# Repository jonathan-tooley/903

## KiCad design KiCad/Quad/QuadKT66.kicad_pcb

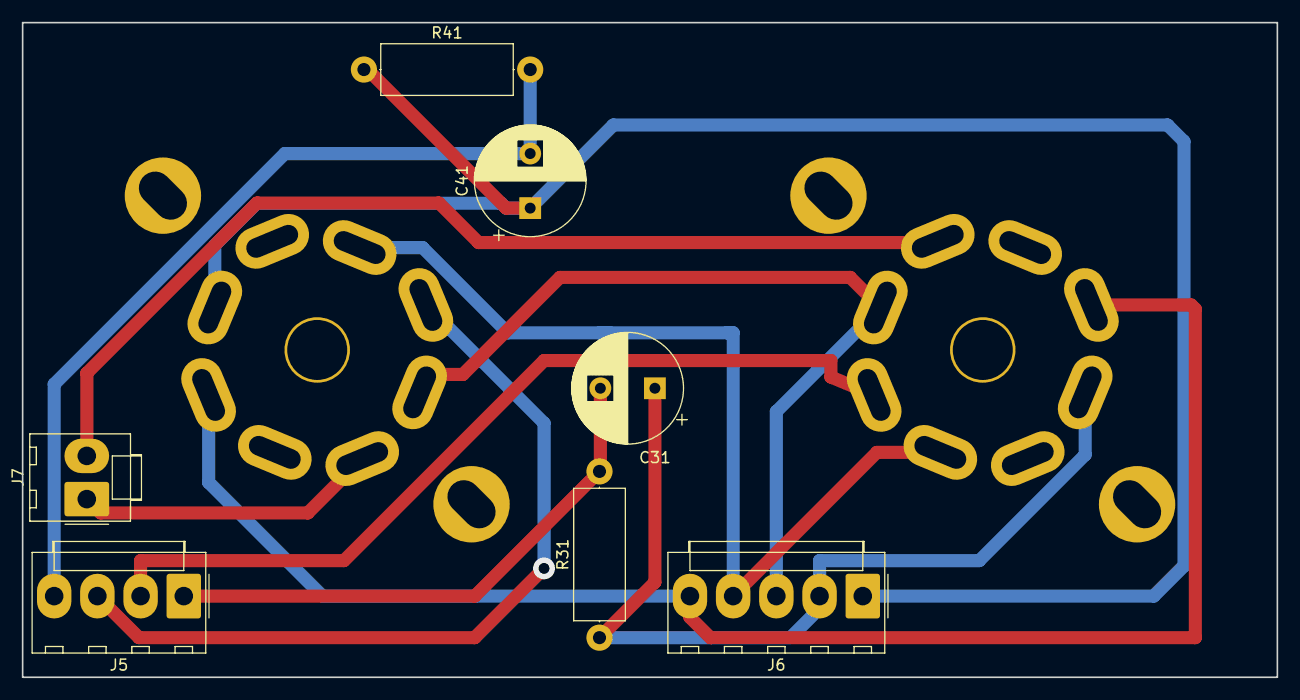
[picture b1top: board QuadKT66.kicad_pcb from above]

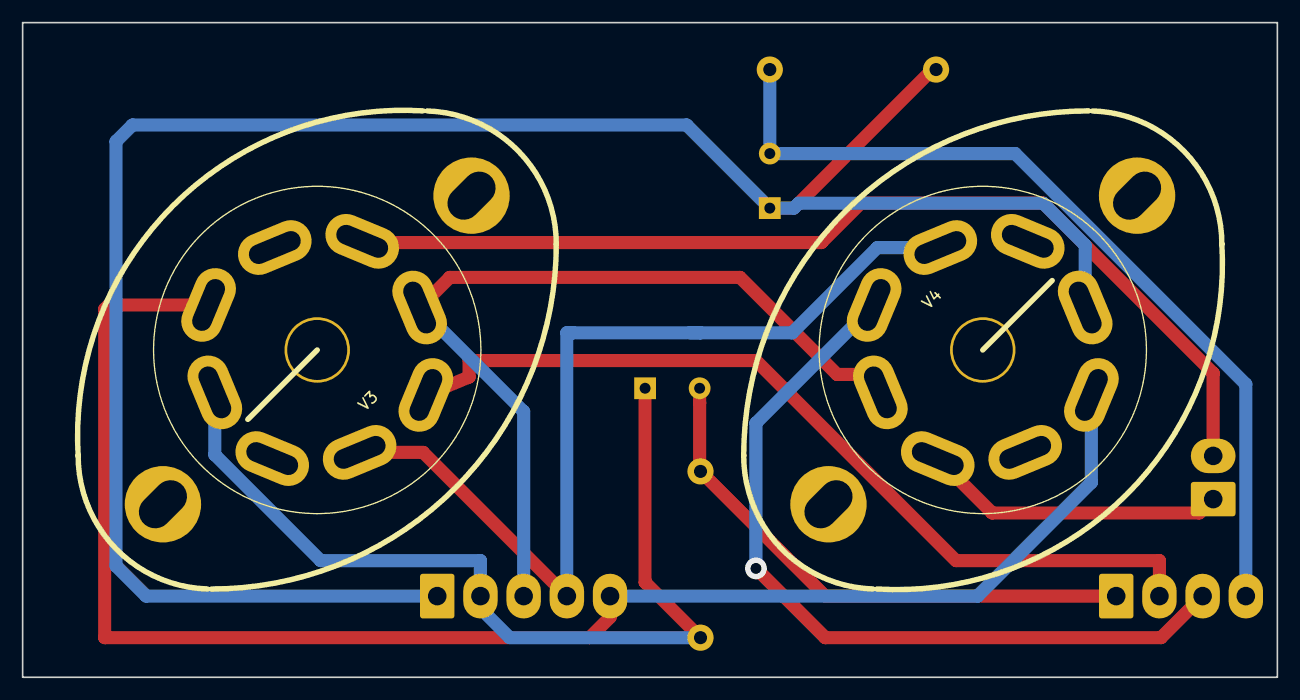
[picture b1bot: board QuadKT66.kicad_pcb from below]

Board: 2 copper layers, 115.0 x 60.0 mm, 9 parts (2 on the bottom side), 11 nets.

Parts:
C31, C41: 470u; CP_Radial_D10.0mm_P5.00mm
J5: Molex_KK-396_A-41791-0004_1x04_P3.96mm_Vertical
J6: Molex_KK-396_A-41791-0005_1x05_P3.96mm_Vertical
J7: Molex_KK-396_A-41791-0002_1x02_P3.96mm_Vertical
R31, R41: 470 5W; R_Axial_DIN0414_L11.9mm_D4.5mm_P15.24mm_Horizontal
V3, V4: KT66; Valve_Octal

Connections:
/+6.3v: J6.4, V3.2, V4.2
/+330v: J6.3, V3.4, V4.4
/-6.3v: J6.5, V3.7, V4.7
/OPT/U: C31.2, J5.1, R31.2
/OPT/W: C41.2, J5.4, R41.2
/OPT/X: J5.3, V4.3
/OPT/Z: J5.2, V3.3
/PowerSupply/K3: C31.1, J6.2, R31.1, V3.8
/PowerSupply/K4: C41.1, J6.1, R41.1, V4.8
/V3: J7.2, V3.5
/V4: J7.1, V4.5

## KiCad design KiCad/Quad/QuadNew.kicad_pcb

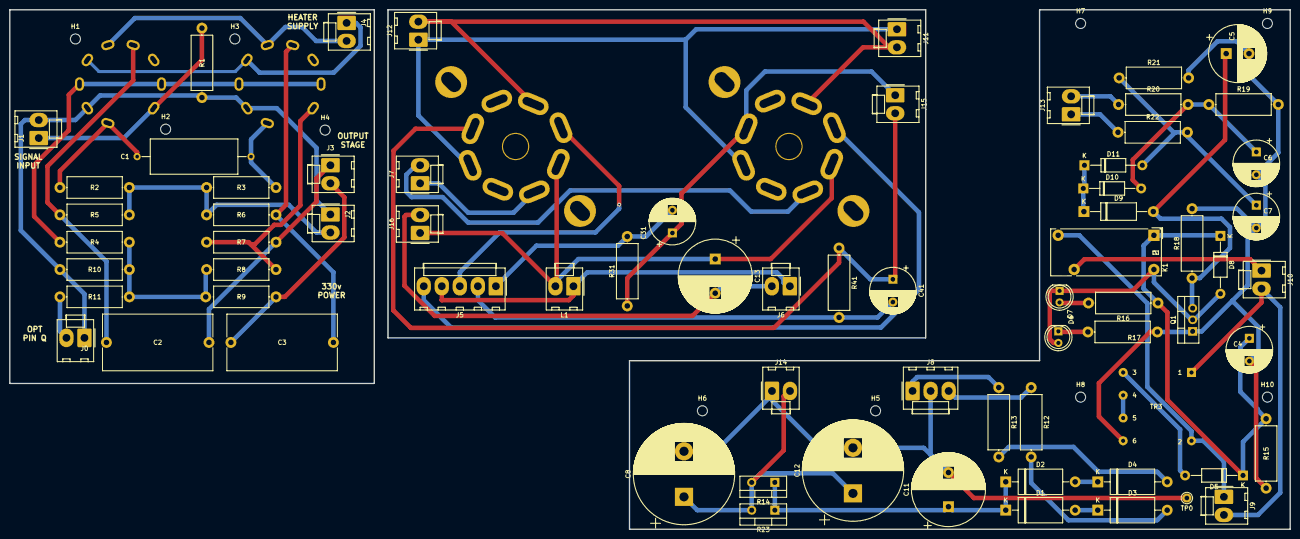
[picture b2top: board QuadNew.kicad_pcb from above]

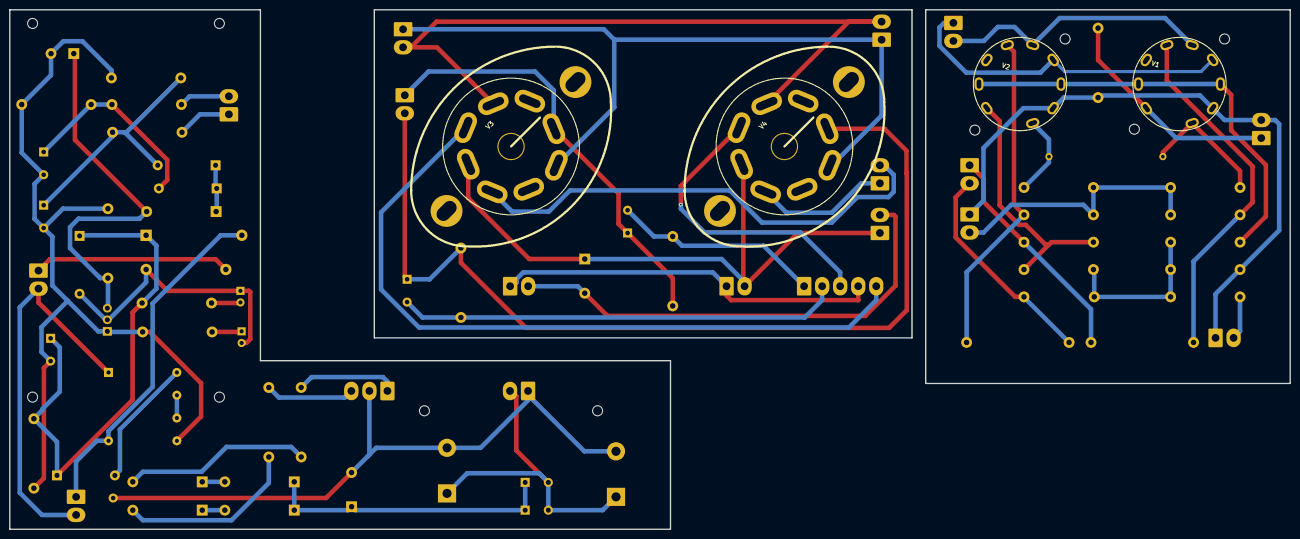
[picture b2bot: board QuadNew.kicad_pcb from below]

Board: 2 copper layers, 281.0 x 114.0 mm, 85 parts (4 on the bottom side), 43 nets.

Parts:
C1: 0.1u; C_Axial_L19.0mm_D7.5mm_P25.00mm_Horizontal
C2, C3: 0.1u; C_Rect_L24.0mm_W12.2mm_P22.50mm_MKT
C4, C6, C7, C31, C41: 470u; CP_Radial_D10.0mm_P5.00mm
C5: 10u; CP_Radial_D12.5mm_P5.00mm
C8, C12: 220u 450v; CP_Radial_D22.0mm_P10.00mm_SnapIn
C11, C13: 47u 450v; CP_Radial_D16.0mm_P7.50mm
D1, D2, D4: D_DO-27_P15.24mm_Horizontal
D3: 1N5408; D_DO-27_P15.24mm_Horizontal
D5, D8, D10, D11: 1N4004; D_DO-41_SOD81_P12.70mm_Horizontal
D6, D7: LED; LED_D5.0mm
D9: 10v 5W; D_DO-15_P15.24mm_Horizontal
H1, H2, H3, H4, H5, H6, H7, H8, H9, H10: MountingHole_2.2mm_M2_ISO7380
J0, J1, J2, J3, J4, J6, J7, J9, J10, J11, J12, J13, J14, J15, J16: Molex_KK-396_A-41791-0002_1x02_P3.96mm_Vertical
J5: Molex_KK-396_A-41791-0005_1x05_P3.96mm_Vertical
J8: Molex_KK-396_A-41791-0003_1x03_P3.96mm_Vertical
K1: ADW11; Relay_1P1T_NO_10x24x18.8mm_Panasonic_ADW11xxxxW_THT
L1: Molex_KK-396_A-41791-0002_1x02_P3.96mm_Vertical
Q1: TIC106; TO-220-3_Vertical
R1: 150M; R_Axial_DIN0414_L11.9mm_D4.5mm_P15.24mm_Horizontal
R2, R3: 1M; R_Axial_DIN0414_L11.9mm_D4.5mm_P15.24mm_Horizontal
R4, R7, R9: 680R; R_Axial_DIN0414_L11.9mm_D4.5mm_P15.24mm_Horizontal
R5, R6: 180k; R_Axial_DIN0414_L11.9mm_D4.5mm_P15.24mm_Horizontal
R8: 2k7; R_Axial_DIN0414_L11.9mm_D4.5mm_P15.24mm_Horizontal
R10: 100R; R_Axial_DIN0414_L11.9mm_D4.5mm_P15.24mm_Horizontal
R11: 470; R_Axial_DIN0414_L11.9mm_D4.5mm_P15.24mm_Horizontal
R12, R13: 47 5W; R_Axial_DIN0414_L11.9mm_D4.5mm_P15.24mm_Horizontal
R14, R23: 270 20W; TO-220-2_Vertical
R15: 1K5; R_Axial_DIN0414_L11.9mm_D4.5mm_P15.24mm_Horizontal
R16, R17: 1K2; R_Axial_DIN0414_L11.9mm_D4.5mm_P15.24mm_Horizontal
R18: 2K7; R_Axial_DIN0414_L11.9mm_D4.5mm_P15.24mm_Horizontal
R19, R21: 6K8; R_Axial_DIN0414_L11.9mm_D4.5mm_P15.24mm_Horizontal
R20, R22: 18K; R_Axial_DIN0414_L11.9mm_D4.5mm_P15.24mm_Horizontal
R31, R41: 470 5W; R_Axial_DIN0414_L11.9mm_D4.5mm_P15.24mm_Horizontal
TP0: GROUND; Pin_D1.0mm_L10.0mm
TR3: Transformer_22x22.7
V1, V2: EF86; Valve_ECC-82
V3, V4: KT66; Valve_Octal

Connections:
/0v: C8.2, C11.2, C12.2, C13.2, J0.1, J1.2, J2.1, J6.2, J8.2, J14.1, J16.2, R1.2, R10.2, TP0.1, V1.2, V2.2
/+6.3v: J4.1, J11.2, J12.2, V1.4, V2.4, V3.2, V4.2
/+330v: C13.1, J2.2, J16.1, L1.2, R2.2, R3.1, R5.2, R6.1, V3.4, V4.4
/+340v: C8.1, C12.1, J5.4, J6.1, J14.2, L1.1, R14.2, R23.2
/-6.3v: J4.2, J11.1, J12.1, V1.5, V2.5, V3.7, V4.7
/OPT/Q: J0.2, R11.1
/OPT/U: C31.2, J5.1, R31.2
/OPT/W: C41.2, J5.2, R41.2
/OPT/X: J5.3, V4.3
/OPT/Z: J5.5, V3.3
/PowerSupply/Com: J10.1, K1.5
/PowerSupply/HT1: J8.1, R13.1
/PowerSupply/HT2: J8.3, R12.1
/PowerSupply/K3: C31.1, J13.2, J15.1, R20.1, R31.1, V3.8
/PowerSupply/K4: C41.1, J13.1, J15.2, R22.1, R41.1, V4.8
/PowerSupply/L: J9.2, J10.2, TR3.1
/PowerSupply/N: J9.1, K1.3, TR3.2
/Signal/FA: R7.2, R8.1, V2.9
/Signal/FB: R4.2, R8.2, R9.1, R10.1, R11.2
/Signal/K: R4.1, V1.3, V1.8, V2.3, V2.8
/V3: C2.2, J3.1, J7.2, R7.1, V3.5
/V4: C3.1, J3.2, J7.1, R9.2, V4.5
unnamed: C1.1, R2.1, V1.1
unnamed: C1.2, R3.2, V2.1
unnamed: C2.1, R5.1, V1.6
unnamed: C3.2, R6.2, V2.6
unnamed: C4.1, D5.1, D8.1, K1.1, R15.1, R16.1
unnamed: C4.2, C5.2, C6.2, C7.2, Q1.1, R15.2, R17.2, R18.2, R19.2, R21.2, TR3.6
unnamed: C5.1, D9.2, Q1.3, R18.1
unnamed: C6.1, D10.2, R19.1, R20.2
unnamed: C7.1, D11.2, R21.1, R22.2
unnamed: C11.1, D1.1, D2.1, R14.1, R23.1
unnamed: D1.2, D3.1
unnamed: D2.2, D4.1
unnamed: D3.2, R12.2
unnamed: D4.2, R13.2
unnamed: D5.2, TR3.3
unnamed: D6.1, D7.2, D8.2, K1.6, Q1.2
unnamed: D6.2, R16.2
unnamed: D7.1, R17.1
unnamed: D9.1, D10.1, D11.1
unnamed: J1.1, R1.1, V1.9
unnamed: TR3.4, TR3.5

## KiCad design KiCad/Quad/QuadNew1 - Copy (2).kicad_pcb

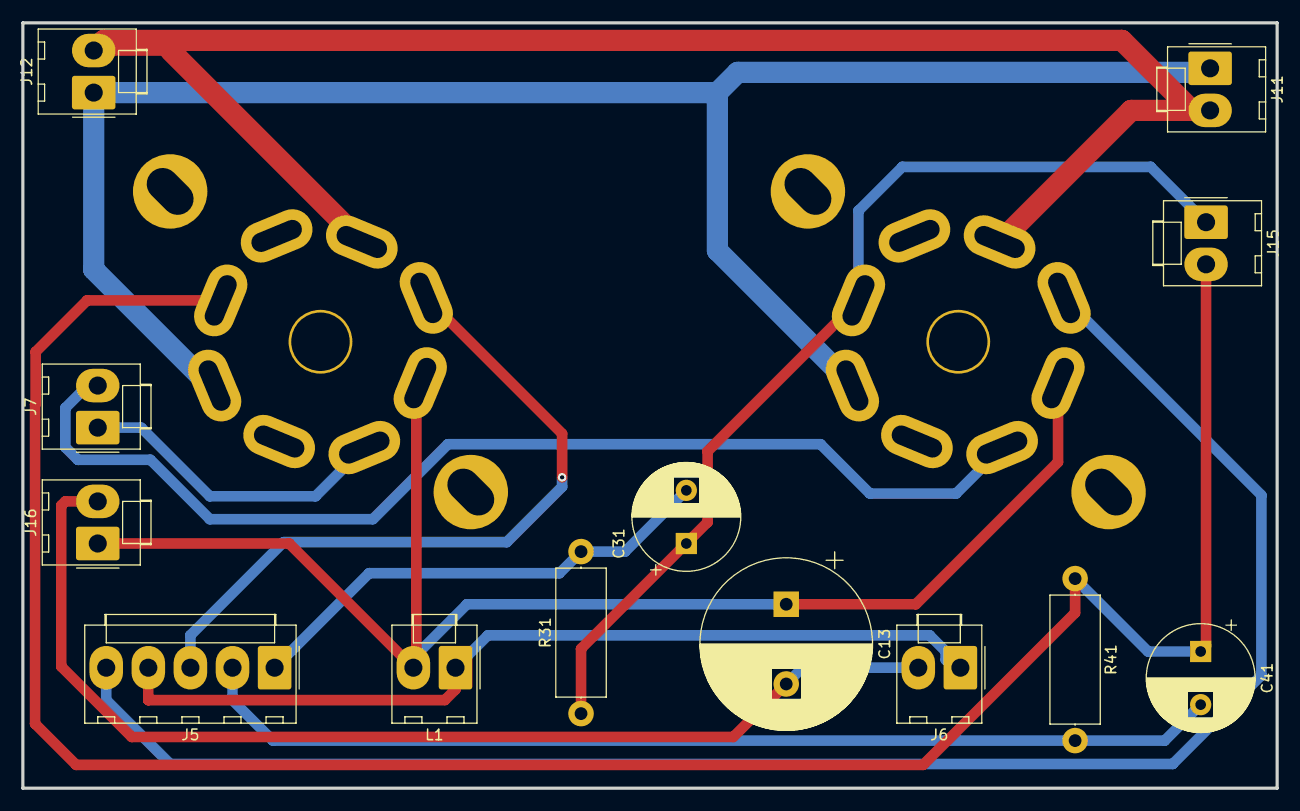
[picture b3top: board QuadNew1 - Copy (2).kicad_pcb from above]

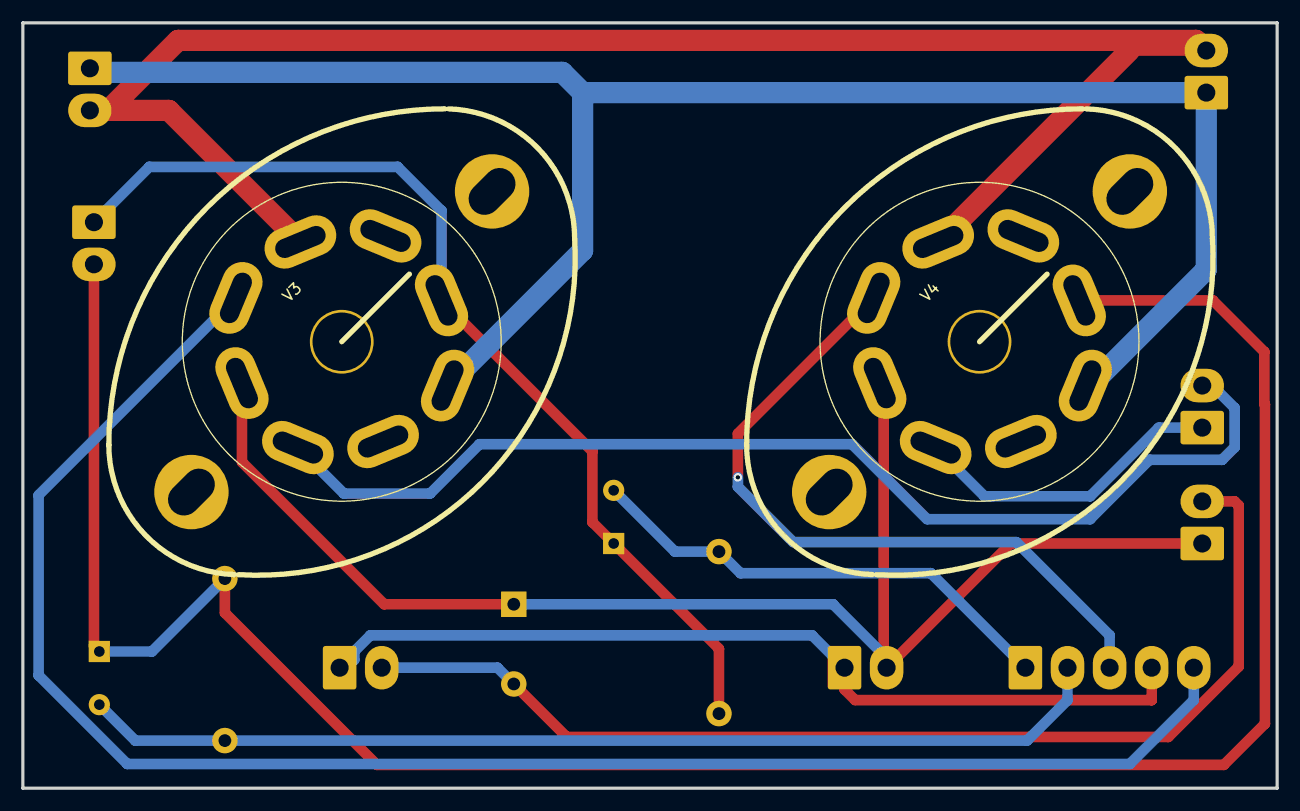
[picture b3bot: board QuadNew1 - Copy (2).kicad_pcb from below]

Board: 2 copper layers, 118.0 x 72.0 mm, 15 parts (2 on the bottom side), 13 nets.

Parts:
C13: 47u 450v; CP_Radial_D16.0mm_P7.50mm
C31, C41: 470u; CP_Radial_D10.0mm_P5.00mm
J5: Molex_KK-396_A-41791-0005_1x05_P3.96mm_Vertical
J6, J7, J11, J12, J15, J16: Molex_KK-396_A-41791-0002_1x02_P3.96mm_Vertical
L1: Molex_KK-396_A-41791-0002_1x02_P3.96mm_Vertical
R31, R41: 470 5W; R_Axial_DIN0414_L11.9mm_D4.5mm_P15.24mm_Horizontal
V3, V4: KT66; Valve_Octal

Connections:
/0v: C13.2, J6.2, J16.2
/+6.3v: J11.2, J12.2, V3.2, V4.2
/+330v: C13.1, J16.1, L1.2, V3.4, V4.4
/+340v: J5.4, J6.1, L1.1
/-6.3v: J11.1, J12.1, V3.7, V4.7
/OPT/U: C31.2, J5.1, R31.2
/OPT/W: C41.2, J5.2, R41.2
/OPT/X: J5.3, V4.3
/OPT/Z: J5.5, V3.3
/PowerSupply/K3: C31.1, J15.1, R31.1, V3.8
/PowerSupply/K4: C41.1, J15.2, R41.1, V4.8
/V3: J7.2, V3.5
/V4: J7.1, V4.5

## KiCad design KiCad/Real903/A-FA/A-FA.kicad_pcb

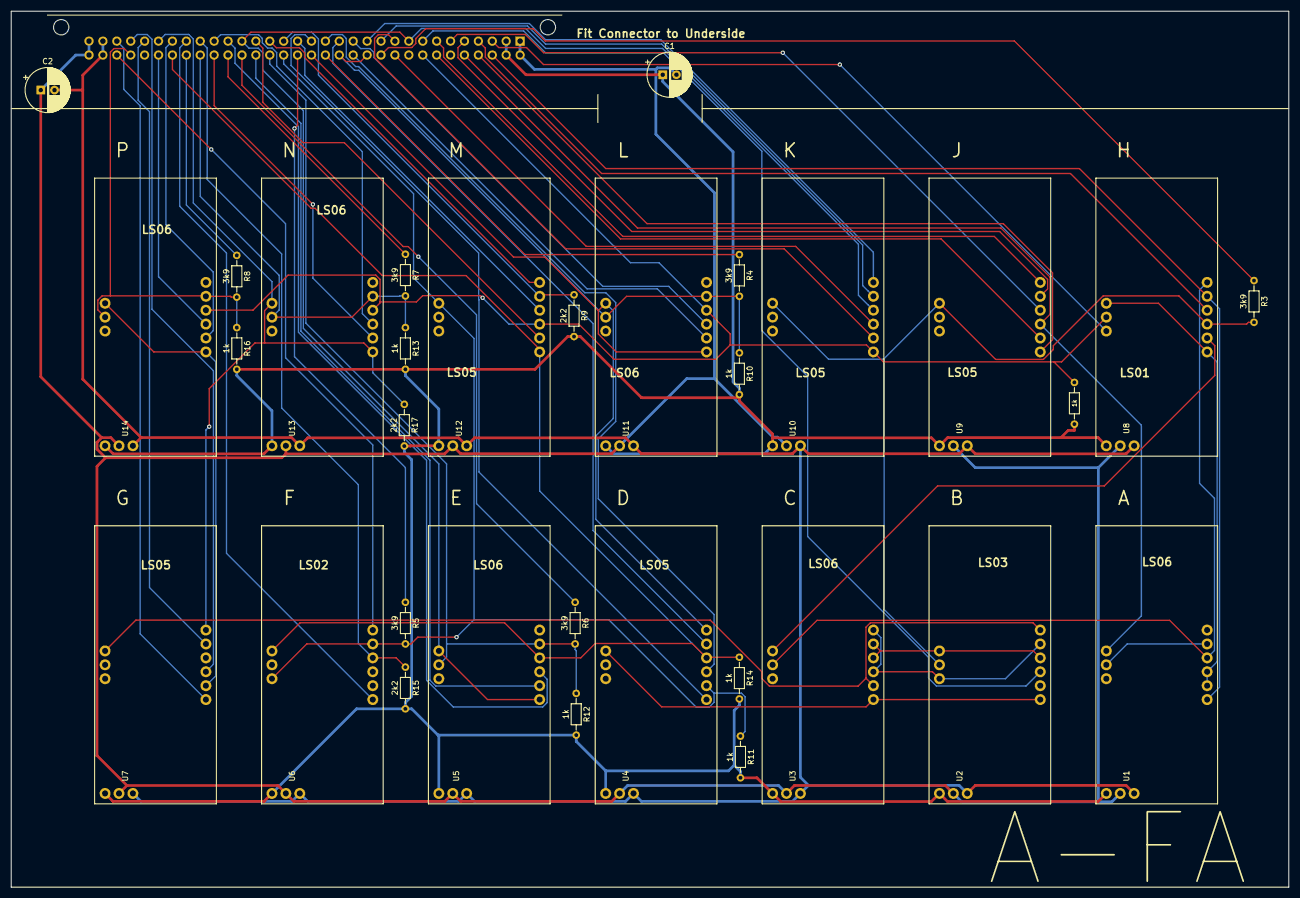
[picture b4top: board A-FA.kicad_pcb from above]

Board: 2 copper layers, 233.3 x 160.0 mm, 33 parts (1 on the bottom side), 64 nets.

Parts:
C1, C2: "6u8"; CP_Radial_D8.0mm_P2.50mm
J1: J1; DIN41612_B_2x32_Horizontal
R3, R4, R5, R6, R7, R8: 3k9; R_Axial_DIN0204_L3.6mm_D1.6mm_P7.62mm_Horizontal
R9, R15, R17: 2k2; R_Axial_DIN0204_L3.6mm_D1.6mm_P7.62mm_Horizontal
R10, R11, R12, R13, R14, R16, R99: 1k; R_Axial_DIN0204_L3.6mm_D1.6mm_P7.62mm_Horizontal
U1, U3, U5, U11, U13, U14: LS06; LSA
U2: LS03; LSA
U4, U7, U9, U10, U12: LS05; LSA
U6: LS02; LSA
U8: LS01; LSA

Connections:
6v: C1.1, J1.2, J1.B, R9.2, R10.2, R11.2, R12.2, R13.2, R14.2, R15.2, R16.2, R17.2, R99.2, U1.21, U2.21, U3.21, U4.21, U5.21, U6.21, U7.21, U8.21, U9.21, U10.21, U11.21, U12.21, U13.21, U14.21
ATF: J1.28, U7.5
An: J1.27, R17.1, U7.6, U13.1, U13.13
An-7: J1.12, U10.6
Cn: J1.3, U8.11
Cn-1: J1.C, U1.1, U8.5
DTF: J1.29, U7.3
FTG: J1.6, U9.4
Fn: J1.E, U1.13, U9.3
FnL: J1.D, U9.1
FnR: J1.5, U9.5
GND: C1.2, C2.1, J1.1, J1.32, J1.A, J1.AL, U1.22, U2.22, U3.22, U4.22, U5.22, U6.22, U7.22, U8.22, U9.22, U10.22, U11.22, U12.22, U13.22, U14.22
GTA: J1.23, U13.3
GTJ: J1.13, U11.3
GTM: J1.17, U12.4
GTQ: J1.AE, U14.3
Gn: J1.J, R99.1, U8.12, U10.1, U11.4, U12.3, U13.4, U14.4
IIn: J1.25, U6.1
IPn: J1.9, J1.21, U5.1, U5.13, U10.4
JTF: J1.14, U4.5
Jn: J1.T, U4.6, U11.1, U11.13
LTG: J1.H, U9.2
MTF: J1.15, U4.3
MTIP: J1.22, U5.3
Mn: J1.AD, R14.1, U4.4, U5.4, U6.13, U12.1
Neg6v: C2.2, J1.31, J1.AK, U1.23, U2.23, U3.23, U4.23, U5.23, U6.23, U7.23, U8.23, U9.23, U10.23, U11.23, U12.23, U13.23, U14.23
unnamed: U1.2, U1.3, U8.1, U8.13
unnamed: U1.4, U3.12, U8.6
unnamed: U1.5, U1.12
unnamed: U3.13, U8.2
PTGa: J1.L, U10.3
PTGb: J1.11, U10.5
QTF: J1.30, U7.1
Qn: U7.2, U14.1, U14.13
RTG: J1.7, U9.6
VTG: J1.8, U2.3
WTM: J1.19, U12.6
Wn: J1.18, R9.1, U12.5
Xn: U2.5, U2.11, U3.3, U3.6
Yn: U2.4, U2.13, U3.4, U3.5
{An}: J1.Z, R7.1
{Gn}: J1.M, R3.1
{IPn}: J1.Y, R6.1
{Jn}: J1.S, R4.1
{Mn}: J1.U, R5.1
{Qn}: J1.AC, R8.1
~A~n: J1.AB, R7.2, R13.1, U13.5, U13.12
~G~n: R3.2, U2.12, U8.3, U9.13, U10.13
~IP~n: J1.W, R6.2, R12.1, U5.5, U5.12
~JTG~: J1.4, U8.4
~J~n: J1.N, J1.R, R4.2, R10.1, U11.5, U11.12
~M~TF: J1.16, U4.1
~M~n: J1.V, R5.2, R11.1, U4.2, U6.5, U6.11, U12.13
~OTA: J1.AA, U13.2
~OTG: J1.10, U10.2
~OTIP: J1.X, U5.2
~OTJ: J1.P, U11.2
~OTM: J1.20, U12.2
~OTQ: J1.26, U14.2
~Q~n: J1.AH, R8.2, R16.1, U14.5, U14.12
~STORE~n: J1.AJ, U6.6
~STORE~nx: J1.24, R15.1, U6.4
~X~n: U2.1, U3.1, U4.13
~Y~n: U2.6, U3.2, U7.13
